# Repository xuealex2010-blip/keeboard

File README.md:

# Keeboard
Hack Club Sponsored DIY Keyboard

Hey, thanks for checking this out, this is my own attempt at creating a DIY 75% Low Profile Mechanical Keyboard.

More details about the process can be found in the Journal Logs.

## CAD
https://cad.onshape.com/documents/ea891d14d2da634eb3b1d96d/w/6142ce2636ba78c1d8d6bd10/e/d20a11642471013c1442f2cf

I decided to go for an affordable green keycap set since I love the color and its one of the cheapest low profile options.

I used heat set inserts and square nuts to hold the case together, I think that this is better than a large 3D print as its designed to be printed at that size. I used only 2 screw lengths which kept the hardware costs low.

## KiCad
https://kicanvas.org/?repo=https%3A%2F%2Fgithub.com%2Fxuealex2010-blip%2Fkeeboard%2Ftree%2Fmain%2FPCB

### Schematic

The schematic final design uses a very basic layout of all the switches. 
I used a generic connector instead of the PiPico symbol to manage the GPIO positions better. I made sure to double check with the official pinouts.

### PCB

This PCB uses a lot more vias than expected, this was to separate the long traces better, and improve ground fill space.

I also made special edge cuts in the PCB, this is because the low profile layout stabilizers drop deep below the plate that it would collide with the PCB if not so.

## Reflection

This was a fun journey, I learned a lot about keyboards, PCB design, and even some more cad skills in specific use cases.
I wanted to do this project because I thought it would be nice to get a cool mechanical keyboard. This still remains so, but I also realize how much I was able to learn. I also think that the this keyboard is much more than a mechanical keyboard, since it has sentimental value since, well I made it. 
I would like to thank Hack Club for showing me this opportunity, even if I don't get to build it, I have learned a lot.

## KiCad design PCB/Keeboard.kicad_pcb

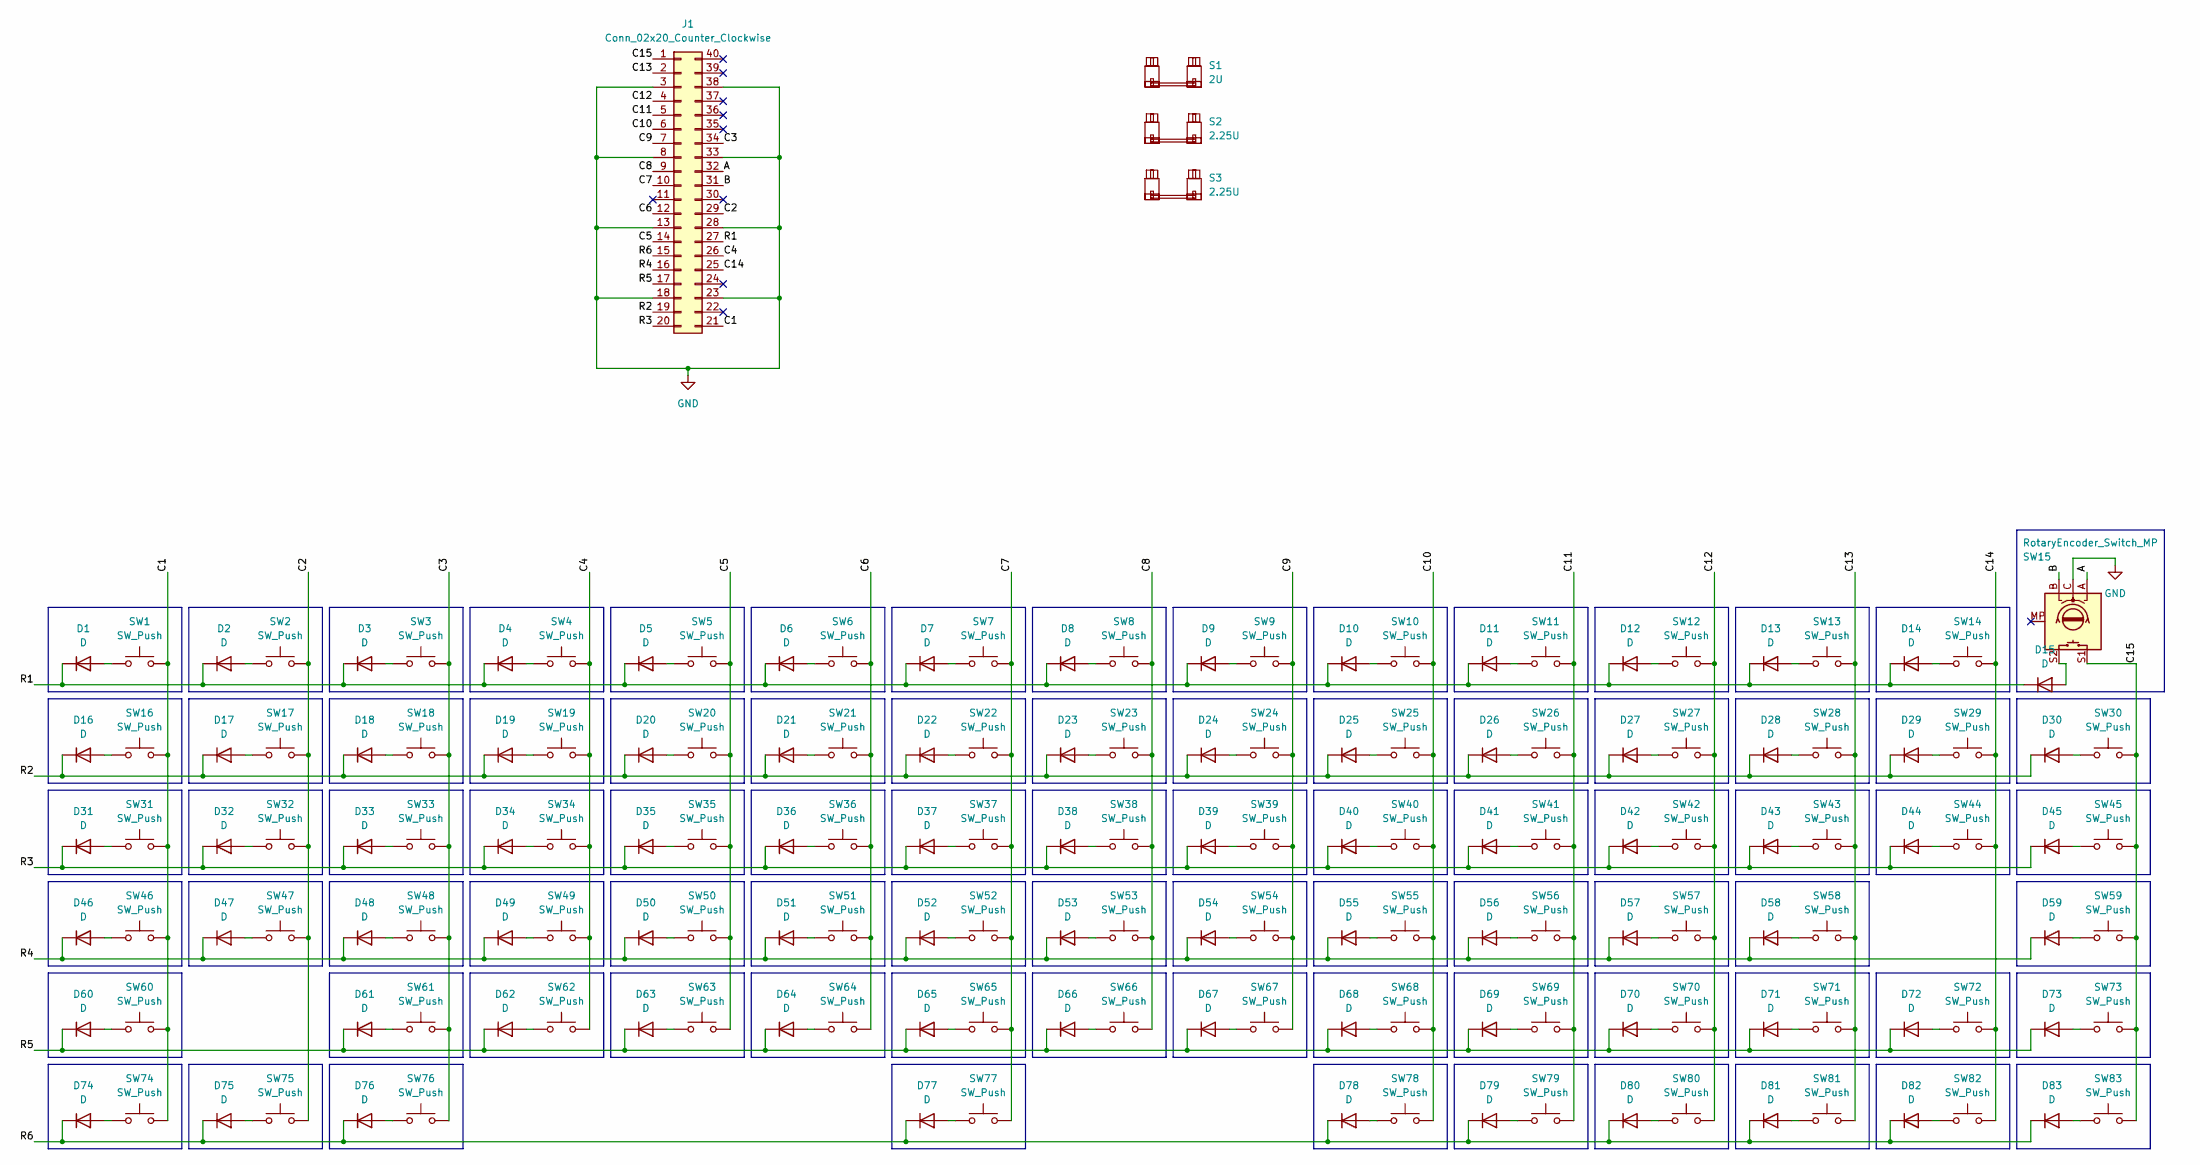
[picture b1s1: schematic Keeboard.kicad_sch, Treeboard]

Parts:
D1, D2, D3, D4, D5, D6, D7, D8, D9, D10, D11, D12, D13, D14, D15, D16, D17, D18, D19, D20, D21, D22, D23, D24, D25, D26, D27, D28, D29, D30, D31, D32, D33, D34, D35, D36, D37, D38, D39, D40, D41, D42, D43, D44, D45, D46, D47, D48, D49, D50, D51, D52, D53, D54, D55, D56, D57, D58, D59, D60, D61, D62, D63, D64, D65, D66, D67, D68, D69, D70, D71, D72, D73, D74, D75, D76, D77, D78, D79, D80, D81, D82, D83: D; D_SOD-123
J1: Conn_02x20_Counter_Clockwise; RaspberryPi_Pico_Header
S1: 2U; STAB_Combo_2u
S2, S3: 2.25U; STAB_Combo_2.25U
SW1, SW2, SW3, SW4, SW5, SW6, SW7, SW8, SW9, SW10, SW11, SW12, SW13, SW14, SW16, SW17, SW18, SW19, SW20, SW21, SW22, SW23, SW24, SW25, SW26, SW27, SW28, SW29, SW30, SW31, SW32, SW33, SW34, SW35, SW36, SW37, SW38, SW39, SW40, SW41, SW42, SW43, SW44, SW45, SW46, SW47, SW48, SW49, SW50, SW51, SW52, SW53, SW54, SW55, SW56, SW57, SW58, SW59, SW60, SW61, SW62, SW63, SW64, SW65, SW66, SW67, SW68, SW69, SW70, SW71, SW72, SW73, SW74, SW75, SW76, SW77, SW78, SW79, SW80, SW81, SW82, SW83: SW_Push; SW_Combo2_MX_Choc
SW15: RotaryEncoder_Switch_MP; ROT_Alps_EC11E-Switch

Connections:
/A: J1.32, SW15.A
/B: J1.31, SW15.B
/C1: J1.21, SW1.1, SW16.1, SW31.1, SW46.1, SW60.1, SW74.1
/C2: J1.29, SW2.1, SW17.1, SW32.1, SW47.1, SW75.1
/C3: J1.34, SW3.1, SW18.1, SW33.1, SW48.1, SW61.1, SW76.1
/C4: J1.26, SW4.1, SW19.1, SW34.1, SW49.1, SW62.1
/C5: J1.14, SW5.1, SW20.1, SW35.1, SW50.1, SW63.1
/C6: J1.12, SW6.1, SW21.1, SW36.1, SW51.1, SW64.1
/C7: J1.10, SW7.1, SW22.1, SW37.1, SW52.1, SW65.1, SW77.1
/C8: J1.9, SW8.1, SW23.1, SW38.1, SW53.1, SW66.1
/C9: J1.7, SW9.1, SW24.1, SW39.1, SW54.1, SW67.1
/C10: J1.6, SW10.1, SW25.1, SW40.1, SW55.1, SW68.1, SW78.1
/C11: J1.5, SW11.1, SW26.1, SW41.1, SW56.1, SW69.1, SW79.1
/C12: J1.4, SW12.1, SW27.1, SW42.1, SW57.1, SW70.1, SW80.1
/C13: J1.2, SW13.1, SW28.1, SW43.1, SW58.1, SW71.1, SW81.1
/C14: J1.25, SW14.1, SW29.1, SW44.1, SW72.1, SW82.1
/C15: J1.1, SW15.S1, SW30.1, SW45.1, SW59.1, SW73.1, SW83.1
/R1: D1.1 (K), D2.1 (K), D3.1 (K), D4.1 (K), D5.1 (K), D6.1 (K), D7.1 (K), D8.1 (K), D9.1 (K), D10.1 (K), D11.1 (K), D12.1 (K), D13.1 (K), D14.1 (K), D15.1 (K), J1.27
/R2: D16.1 (K), D17.1 (K), D18.1 (K), D19.1 (K), D20.1 (K), D21.1 (K), D22.1 (K), D23.1 (K), D24.1 (K), D25.1 (K), D26.1 (K), D27.1 (K), D28.1 (K), D29.1 (K), D30.1 (K), J1.19
/R3: D31.1 (K), D32.1 (K), D33.1 (K), D34.1 (K), D35.1 (K), D36.1 (K), D37.1 (K), D38.1 (K), D39.1 (K), D40.1 (K), D41.1 (K), D42.1 (K), D43.1 (K), D44.1 (K), D45.1 (K), J1.20
/R4: D46.1 (K), D47.1 (K), D48.1 (K), D49.1 (K), D50.1 (K), D51.1 (K), D52.1 (K), D53.1 (K), D54.1 (K), D55.1 (K), D56.1 (K), D57.1 (K), D58.1 (K), D59.1 (K), J1.16
/R5: D60.1 (K), D61.1 (K), D62.1 (K), D63.1 (K), D64.1 (K), D65.1 (K), D66.1 (K), D67.1 (K), D68.1 (K), D69.1 (K), D70.1 (K), D71.1 (K), D72.1 (K), D73.1 (K), J1.17
/R6: D74.1 (K), D75.1 (K), D76.1 (K), D77.1 (K), D78.1 (K), D79.1 (K), D80.1 (K), D81.1 (K), D82.1 (K), D83.1 (K), J1.15
GND: J1.3, J1.8, J1.13, J1.18, J1.23, J1.28, J1.33, J1.38, SW15.C
unnamed: D1.2 (A), SW1.2
unnamed: D2.2 (A), SW2.2
unnamed: D3.2 (A), SW3.2
unnamed: D4.2 (A), SW4.2
unnamed: D5.2 (A), SW5.2
unnamed: D6.2 (A), SW6.2
unnamed: D7.2 (A), SW7.2
unnamed: D8.2 (A), SW8.2
unnamed: D9.2 (A), SW9.2
unnamed: D10.2 (A), SW10.2
unnamed: D11.2 (A), SW11.2
unnamed: D12.2 (A), SW12.2
unnamed: D13.2 (A), SW13.2
unnamed: D14.2 (A), SW14.2
unnamed: D15.2 (A), SW15.S2
unnamed: D16.2 (A), SW16.2
unnamed: D17.2 (A), SW17.2
unnamed: D18.2 (A), SW18.2
unnamed: D19.2 (A), SW19.2
unnamed: D20.2 (A), SW20.2
unnamed: D21.2 (A), SW21.2
unnamed: D22.2 (A), SW22.2
unnamed: D23.2 (A), SW23.2
unnamed: D24.2 (A), SW24.2
unnamed: D25.2 (A), SW25.2
unnamed: D26.2 (A), SW26.2
unnamed: D27.2 (A), SW27.2
unnamed: D28.2 (A), SW28.2
unnamed: D29.2 (A), SW29.2
unnamed: D30.2 (A), SW30.2
unnamed: D31.2 (A), SW31.2
unnamed: D32.2 (A), SW32.2
unnamed: D33.2 (A), SW33.2
unnamed: D34.2 (A), SW34.2
unnamed: D35.2 (A), SW35.2
unnamed: D36.2 (A), SW36.2
unnamed: D37.2 (A), SW37.2
unnamed: D38.2 (A), SW38.2
unnamed: D39.2 (A), SW39.2
unnamed: D40.2 (A), SW40.2
unnamed: D41.2 (A), SW41.2
unnamed: D42.2 (A), SW42.2
unnamed: D43.2 (A), SW43.2
unnamed: D44.2 (A), SW44.2
unnamed: D45.2 (A), SW45.2
unnamed: D46.2 (A), SW46.2
unnamed: D47.2 (A), SW47.2
unnamed: D48.2 (A), SW48.2
unnamed: D49.2 (A), SW49.2
unnamed: D50.2 (A), SW50.2
unnamed: D51.2 (A), SW51.2
unnamed: D52.2 (A), SW52.2
unnamed: D53.2 (A), SW53.2
unnamed: D54.2 (A), SW54.2
unnamed: D55.2 (A), SW55.2
unnamed: D56.2 (A), SW56.2
unnamed: D57.2 (A), SW57.2
unnamed: D58.2 (A), SW58.2
unnamed: D59.2 (A), SW59.2
unnamed: D60.2 (A), SW60.2
unnamed: D61.2 (A), SW61.2
unnamed: D62.2 (A), SW62.2
unnamed: D63.2 (A), SW63.2
unnamed: D64.2 (A), SW64.2
unnamed: D65.2 (A), SW65.2
unnamed: D66.2 (A), SW66.2
unnamed: D67.2 (A), SW67.2
unnamed: D68.2 (A), SW68.2
unnamed: D69.2 (A), SW69.2
unnamed: D70.2 (A), SW70.2
unnamed: D71.2 (A), SW71.2
unnamed: D72.2 (A), SW72.2
unnamed: D73.2 (A), SW73.2
unnamed: D74.2 (A), SW74.2
unnamed: D75.2 (A), SW75.2
unnamed: D76.2 (A), SW76.2
unnamed: D77.2 (A), SW77.2
unnamed: D78.2 (A), SW78.2
unnamed: D79.2 (A), SW79.2
unnamed: D80.2 (A), SW80.2
unnamed: D81.2 (A), SW81.2
unnamed: D82.2 (A), SW82.2
unnamed: D83.2 (A), SW83.2

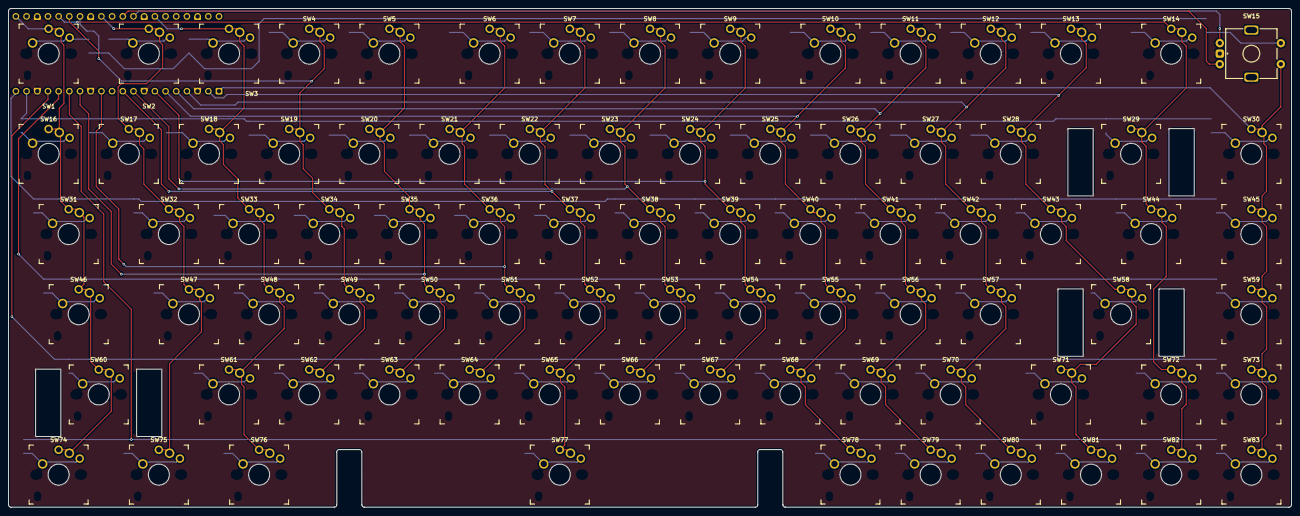
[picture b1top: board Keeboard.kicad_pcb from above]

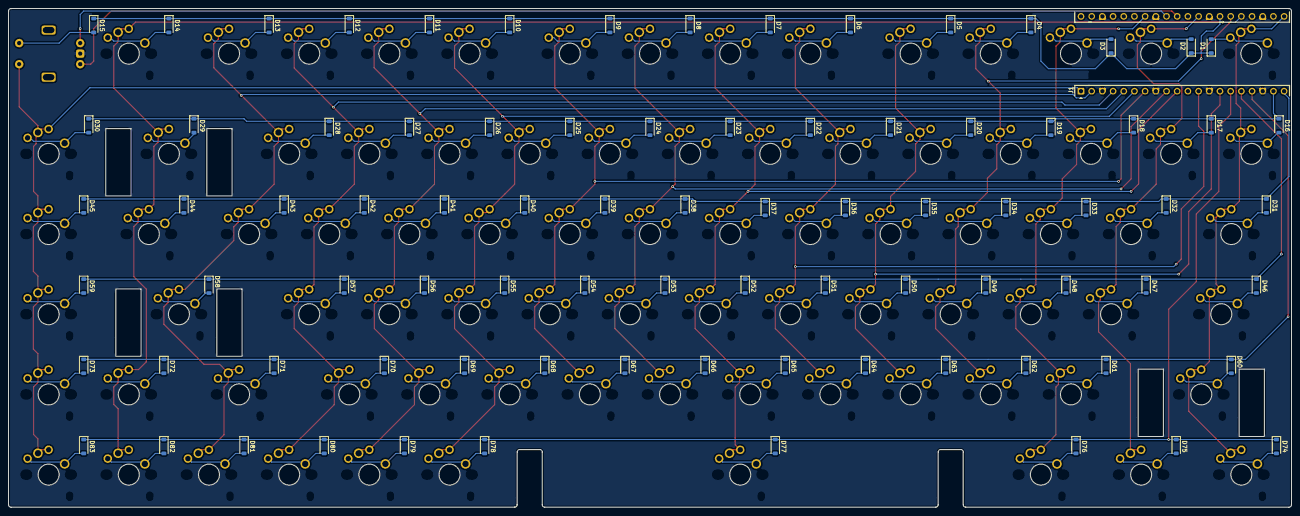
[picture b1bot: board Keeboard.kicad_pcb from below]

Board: 2 copper layers, 304.8 x 118.5 mm, 170 parts (84 on the bottom side), 107 nets.

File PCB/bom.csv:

Designator,Footprint,Quantity,Value,LCSC Part #
"D1, D10, D11, D12, D13, D14, D15, D16, D17, D18, D19, D2, D20, D21, D22, D23, D24, D25, D26, D27, D28, D29, D3, D30, D31, D32, D33, D34, D35, D36, D37, D38, D39, D4, D40, D41, D42, D43, D44, D45, D46, D47, D48, D49, D5, D50, D51, D52, D53, D54, D55, D56, D57, D58, D59, D6, D60, D61, D62, D63, D64, D65, D66, D67, D68, D69, D7, D70, D71, D72, D73, D74, D75, D76, D77, D78, D79, D8, D80, D81, D82, D83, D9",D_SOD-123,83,D,
J1,RaspberryPi_Pico_Header,1,Conn_02x20_Counter_Clockwise,
S1,STAB_Combo_2u,1,2U,
"S2, S3",STAB_Combo_2.25U,2,2.25U,
"SW1, SW10, SW11, SW12, SW13, SW14, SW16, SW17, SW18, SW19, SW2, SW20, SW21, SW22, SW23, SW24, SW25, SW26, SW27, SW28, SW29, SW3, SW30, SW31, SW32, SW33, SW34, SW35, SW36, SW37, SW38, SW39, SW4, SW40, SW41, SW42, SW43, SW44, SW45, SW46, SW47, SW48, SW49, SW5, SW50, SW51, SW52, SW53, SW54, SW55, SW56, SW57, SW58, SW59, SW6, SW60, SW61, SW62, SW63, SW64, SW65, SW66, SW67, SW68, SW69, SW7, SW70, SW71, SW72, SW73, SW74, SW75, SW76, SW77, SW78, SW79, SW8, SW80, SW81, SW82, SW83, SW9",SW_Combo2_MX_Choc,82,SW_Push,
SW15,ROT_Alps_EC11E-Switch,1,RotaryEncoder_Switch_MP,
